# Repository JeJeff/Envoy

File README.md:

# Envoy
Envoy is a numberpad that can also be built as a 20 key macropad with support for four encoders. 

<details>
  <summary>Kicad images</summary>
  
 ### PCB Front

 ### PCB Back
 
</details>

<details>
  <summary>PCB renders</summary>
  
 ### PCB Front

 ### PCB Back
 
</details>

## Key features
* 20 key macro pad or standard number pad configuration
* Both 3 and 5 pin MX style switches supported
* Hot swap sockets
* Four rotary encoders
* QMK controlled
* Vial firmware
* Easy to solder

## Additional information
 * 2 layer PCB
 * Switch plate and back plate designs available
 * Both throughhole and SMD diodes supported
 
## Bill of materials
|Reference | Item                     | Quantity | Notes
|:--------:|--------------------------|:--------:|-------------------------------------
|          | **Plates**               |          |
|          | PCB                      | 1        |
|          | Back plate               | 1        | 
|          | Switch plate             | 1        | Technically optional, but recommended.
|          |                          |          |
|          | **Components to solder** |          |
| D1-D20   | 1N4148 Diode             | 21-24    | Both SMD (SOD-123) and through hole (DO-35) supported.
| U1       | 12x1 male pin header     | 2        | For the pro micro.
| U1       | Pro Micro                | 1        | Or pin compatible controller.
| ENC1-ENC4| EC11 Rotary Encoder      | 4        | 
|          |                          |          |
|          | **Hardware**             |          |
|          | Aluminium cone feet      | 0 or 2   | If you want to raise the back and tilt the pad towards you.
|          | M2 standoff 8mm          | 4        | 
|          | M2 x 6mm flat head screw | 8        | Button head screws also work, could go as short as 4mm.
|          | Rubber feet 8mm diameter | 2 or 4   | Only 2 needed if also using the cone feet.
|          |                          |          |
|          | **Keys and Knobs**       |          |
|          | 2u Stabilizer            | 0-3      | One required for each 2u key, 3 for a standard number pad configuration.
|          | MX Switches              | 17-20    | 
|          | Keycaps                  | 17-20    | 
|          | Encoder knob             | 4        | Matching the encoder, max diameter 18mm.

## Build Guide
* [Long version with descriptions and tips](Build-Guide.md) 
* [Short version which is not much more than a list of steos](Build-Guide-Short.md)

## Firmware
[See the firmware flashing guide](Firmware/Firmware-Flashing.md)

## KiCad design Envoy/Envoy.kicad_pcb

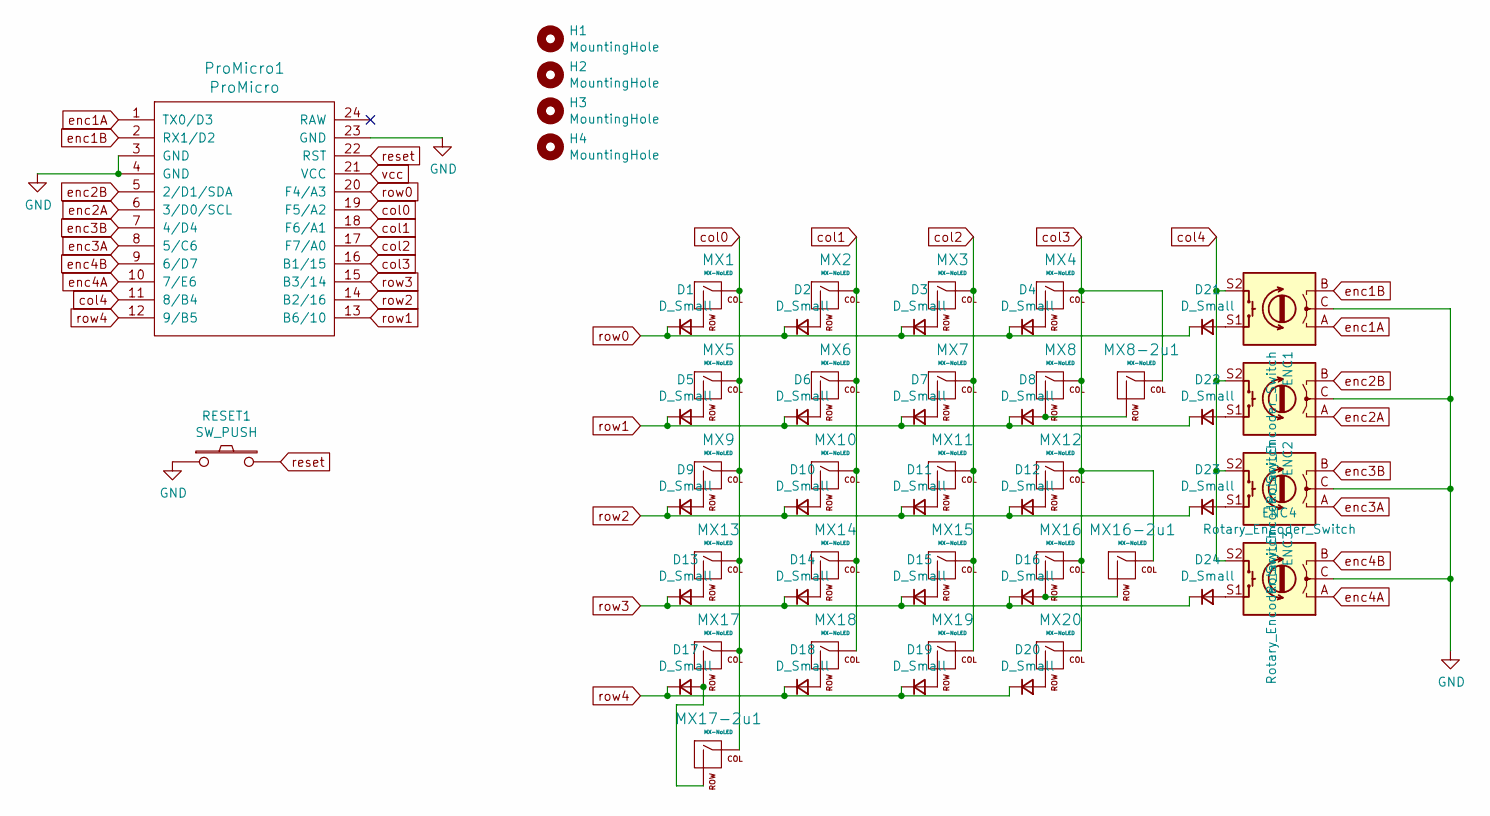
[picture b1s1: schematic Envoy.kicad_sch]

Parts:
D1, D2, D3, D4, D5, D6, D7, D8, D9, D10, D11, D12, D13, D14, D15, D16, D17, D18, D19, D20, D21, D22, D23, D24: D_Small; Diode-Hybrid-Back
ENC1, ENC2: Rotary_Encoder_Switch; RotaryEncoder_EC11-no-legs
ENC3, ENC4: Rotary_Encoder_Switch; RotaryEncoder_EC11
H1, H2, H3, H4: MountingHole; MountingHole_2.5mm
MX1, MX2, MX3, MX5, MX6, MX7, MX9, MX10, MX11, MX13, MX14, MX15, MX19: MX-NoLED; MXOnly-1U-Hotswap
MX4: MX-NoLED; MXOnly-1U-HotswapReversed
MX8, MX12, MX16, MX17: MX-NoLED; MXOnly-1U-Hotswap-2KeyAlternativeLeft
MX8-2u1, MX16-2u1: MX-NoLED; MXOnly-2U-Hotswap-2KeyAlternative
MX17-2u1: MX-NoLED; MXOnly-2U-Hotswap-ReversedStabilizers-Alternative
MX18, MX20: MX-NoLED; MXOnly-1U-HotswapReversed-2KeyAlternativeLeft
ProMicro1: ProMicro; ProMicro_v3
RESET1: SW_PUSH; ResetSW

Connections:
GND: ENC1.C, ENC2.C, ENC3.C, ENC4.C, ProMicro1.3 (GND), ProMicro1.4 (GND), ProMicro1.23 (GND), RESET1.1
unnamed: D1.2 (A), MX1.2 (ROW)
unnamed: D2.2 (A), MX2.2 (ROW)
unnamed: D3.2 (A), MX3.2 (ROW)
unnamed: D4.2 (A), MX4.2 (ROW)
unnamed: D5.2 (A), MX5.2 (ROW)
unnamed: D6.2 (A), MX6.2 (ROW)
unnamed: D7.2 (A), MX7.2 (ROW)
unnamed: D8.2 (A), MX8.2 (ROW), MX8-2u1.2 (ROW)
unnamed: D9.2 (A), MX9.2 (ROW)
unnamed: D10.2 (A), MX10.2 (ROW)
unnamed: D11.2 (A), MX11.2 (ROW)
unnamed: D12.2 (A), MX12.2 (ROW)
unnamed: D13.2 (A), MX13.2 (ROW)
unnamed: D14.2 (A), MX14.2 (ROW)
unnamed: D15.2 (A), MX15.2 (ROW)
unnamed: D16.2 (A), MX16.2 (ROW), MX16-2u1.2 (ROW)
unnamed: D17.2 (A), MX17.2 (ROW), MX17-2u1.2 (ROW)
unnamed: D18.2 (A), MX18.2 (ROW)
unnamed: D19.2 (A), MX19.2 (ROW)
unnamed: D20.2 (A), MX20.2 (ROW)
unnamed: D21.2 (A), ENC1.S1
unnamed: D22.2 (A), ENC2.S1
unnamed: D23.2 (A), ENC3.S1
unnamed: D24.2 (A), ENC4.S1
col0: MX1.1 (COL), MX5.1 (COL), MX9.1 (COL), MX13.1 (COL), MX17.1 (COL), MX17-2u1.1 (COL), ProMicro1.19 (F5/A2)
col1: MX2.1 (COL), MX6.1 (COL), MX10.1 (COL), MX14.1 (COL), MX18.1 (COL), ProMicro1.18 (F6/A1)
col2: MX3.1 (COL), MX7.1 (COL), MX11.1 (COL), MX15.1 (COL), MX19.1 (COL), ProMicro1.17 (F7/A0)
col3: MX4.1 (COL), MX8.1 (COL), MX8-2u1.1 (COL), MX12.1 (COL), MX16.1 (COL), MX16-2u1.1 (COL), MX20.1 (COL), ProMicro1.16 (B1/15)
col4: ENC1.S2, ENC2.S2, ENC3.S2, ENC4.S2, ProMicro1.11 (8/B4)
enc1A: ENC1.A, ProMicro1.1 (TX0/D3)
enc1B: ENC1.B, ProMicro1.2 (RX1/D2)
enc2A: ENC2.A, ProMicro1.6 (3/D0/SCL)
enc2B: ENC2.B, ProMicro1.5 (2/D1/SDA)
enc3A: ENC3.A, ProMicro1.8 (5/C6)
enc3B: ENC3.B, ProMicro1.7 (4/D4)
enc4A: ENC4.A, ProMicro1.10 (7/E6)
enc4B: ENC4.B, ProMicro1.9 (6/D7)
reset: ProMicro1.22 (RST), RESET1.2
row0: D1.1 (K), D2.1 (K), D3.1 (K), D4.1 (K), D21.1 (K), ProMicro1.20 (F4/A3)
row1: D5.1 (K), D6.1 (K), D7.1 (K), D8.1 (K), D22.1 (K), ProMicro1.13 (B6/10)
row2: D9.1 (K), D10.1 (K), D11.1 (K), D12.1 (K), D23.1 (K), ProMicro1.14 (B2/16)
row3: D13.1 (K), D14.1 (K), D15.1 (K), D16.1 (K), D24.1 (K), ProMicro1.15 (B3/14)
row4: D17.1 (K), D18.1 (K), D19.1 (K), D20.1 (K), ProMicro1.12 (9/B5)
vcc: ProMicro1.21 (VCC)

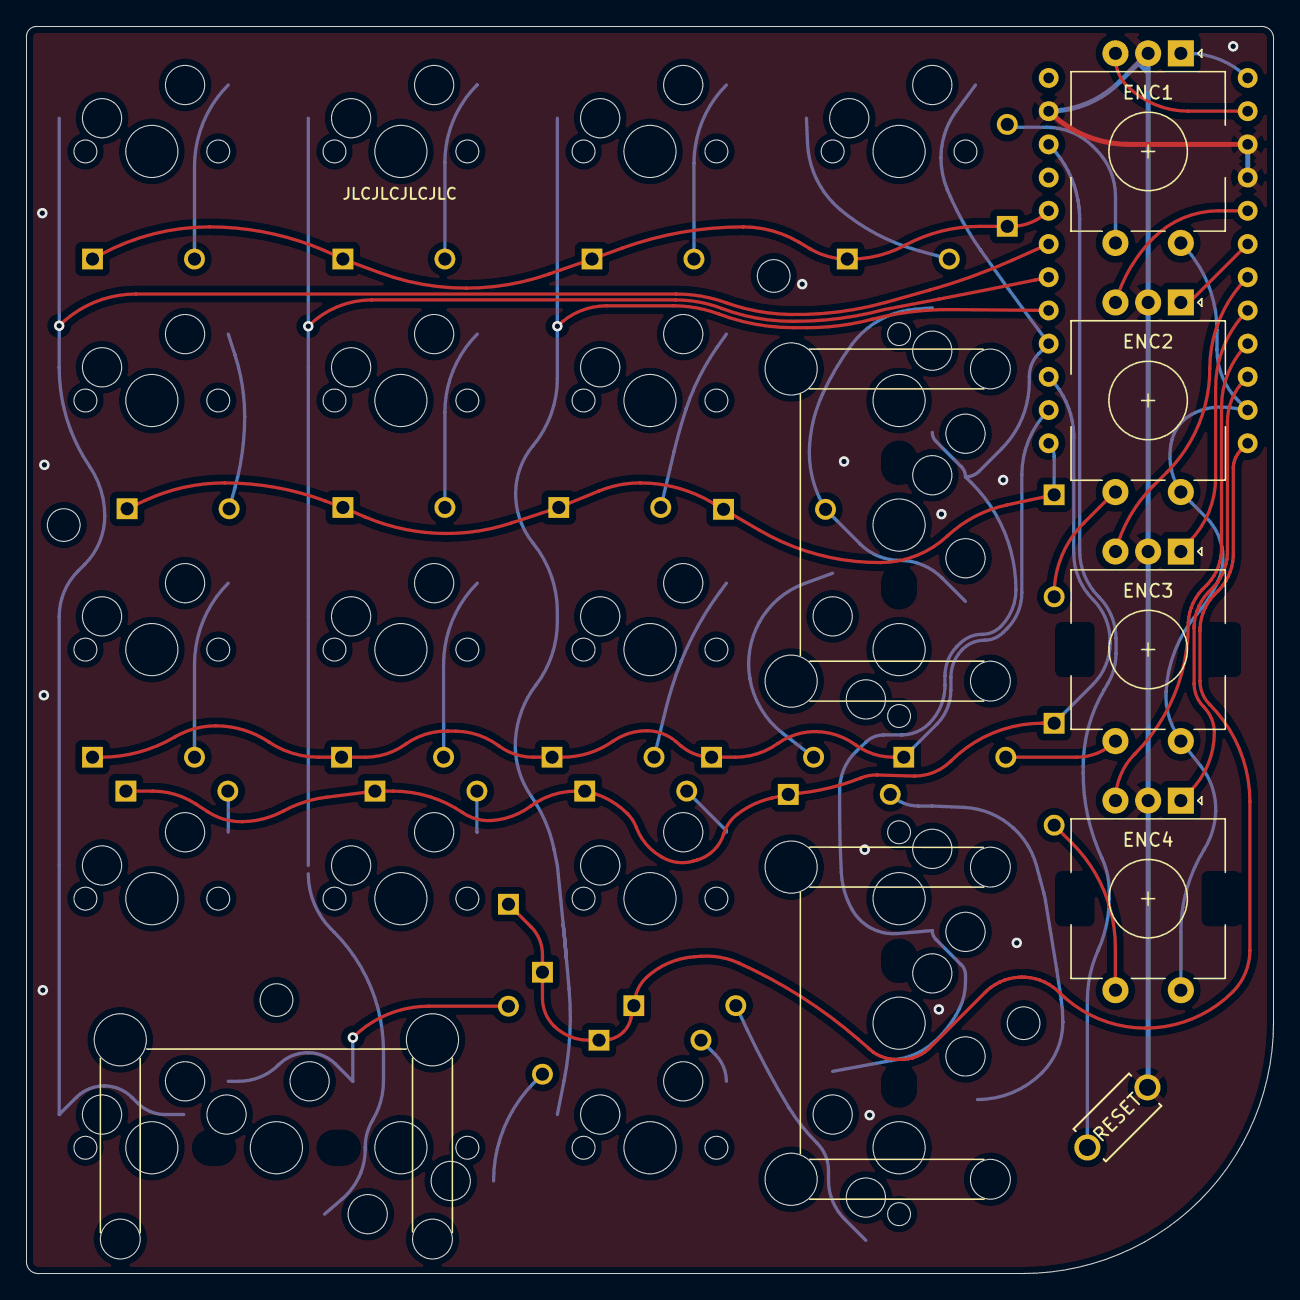
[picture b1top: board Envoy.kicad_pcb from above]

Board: 2 copper layers, 95.4 x 95.4 mm, 57 parts (0 on the bottom side), 44 nets.

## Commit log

2021-09-27 First draft done
2021-10-22 Rev 0.2 including switchplate and backplate
2021-11-01 Fix switchplate cutout sizes
2021-11-01 Move standoff and bumper positioning to make the backplate work easier
2021-11-01 Fix logo on switchplate
2021-11-01 add PCB identifier
2021-11-03 More tweaks to the switchplate cutouts, make switchplate float instead of the PCB, move diodes to give more space to stabs
2021-11-03 update git ignore to not keep autosaves
2021-11-03 Moved most diodes to horizontal layout to enable better access for soldering hotswap sockets
2021-11-03 Increasxed line width in small envoy icon
2021-11-08 curves! Fun curved traces. Prepare rev0.2 gerbers
2021-11-26 Moved feet outwards a bit for additional stability
2021-11-26 Widen feet placement a little more. Bump revision to 1.0
2021-11-27 Moved a standoff hole and the feet. Bumped pcb revision to 1.0
2021-11-27 Bumped switchplate revision to 1.0. No design changes from rev 0.2.
2021-11-27 Final feet position
2021-11-28 Add first images for build guide
2021-11-28 Move images
2021-11-28 Make font slightly bolder so the HASL finish stands more chance of sticking.
2021-11-28 Add vial firmware
2021-11-29 Flash guide images
2021-11-30 design rule exclusions
2021-12-02 6mm standoffs were too short. Modified to 8mm
2021-12-08 Add photos
2021-12-09 added pcb images
2021-12-10 update pcb images
2021-12-10 My edits were bad. Use raw export.
2021-12-10 Fix bad edits
